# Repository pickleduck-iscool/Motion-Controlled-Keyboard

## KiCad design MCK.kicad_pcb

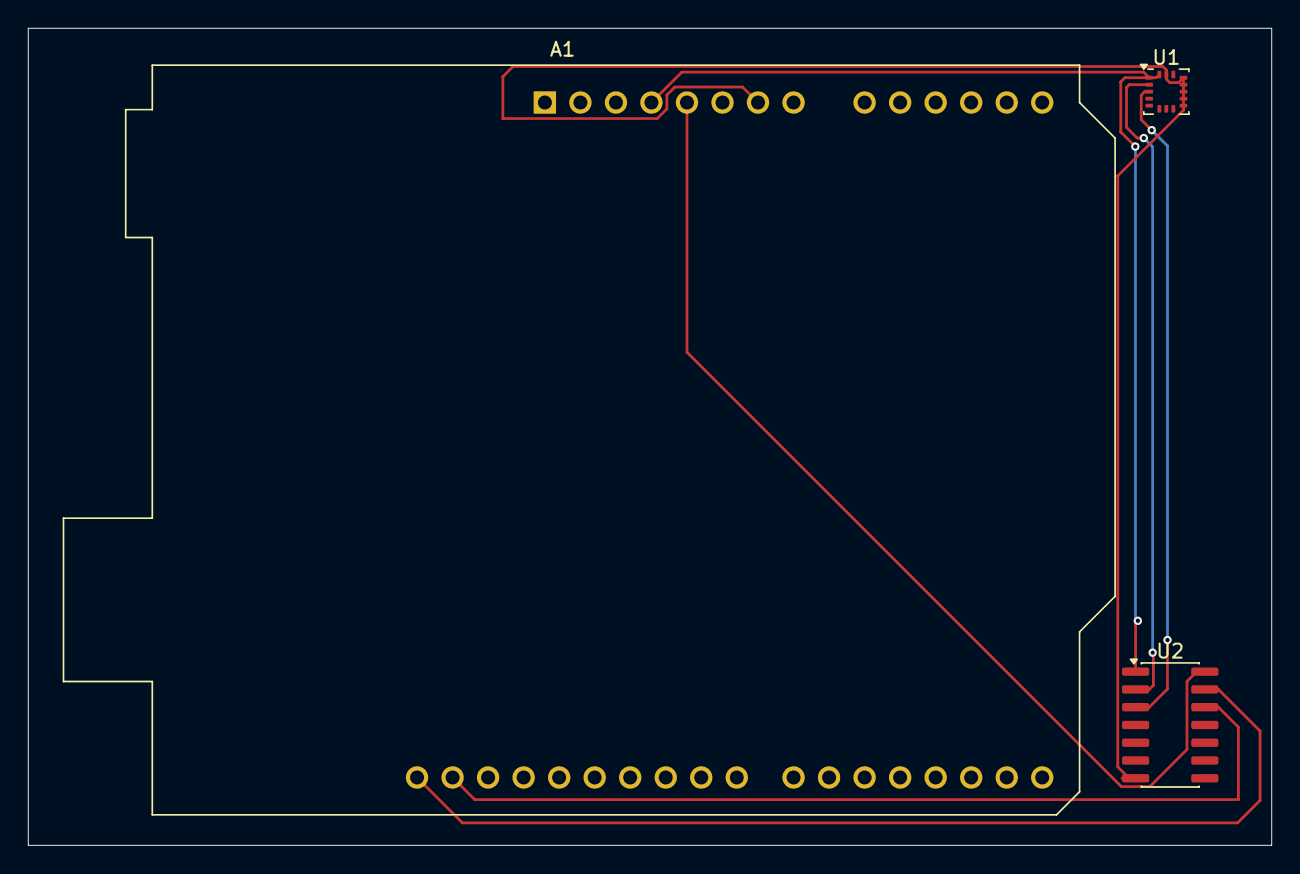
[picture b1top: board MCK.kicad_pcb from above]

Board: 2 copper layers, 88.9 x 58.4 mm, 3 parts (0 on the bottom side), 7 nets.

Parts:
A1: Arduino_Leonardo; Arduino_UNO_R3
U1: ICM-20602; LGA-16_3x3mm_P0.5mm_LayoutBorder3x5y
U2: TXS0104ED; SOIC-14_3.9x8.7mm_P1.27mm

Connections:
unnamed: A1.4 (3V3), U1.1 (VDDIO), U1.16 (VDD), U2.1 (V_{CCA})
unnamed: A1.5 (+5V), U2.14 (V_{CCB})
unnamed: A1.32 (SCL/D3), U2.13 (B1)
unnamed: A1.31 (SDA/D2), U2.12 (B2)
unnamed: U1.2 (SCL/SPC), U2.2 (A1)
unnamed: U1.3 (SDA/SDI), U2.3 (A2)
unnamed: A1.7 (GND), U1.9 (GND), U1.10 (GND), U1.11 (GND), U1.12 (GND), U1.13 (GND), U1.15 (GND), U2.7 (GND)

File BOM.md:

# Hand Motion Keyboard – bill of materials

<!-- Generated by Half Life from project cmv2t30zv083401q3pdh1eyeq. Edits here are overwritten on the next sync. -->
<!-- Generated: 2026-10-12T02:02:27.321Z -->

> [!NOTE]
> This parts list is mirrored from [Half Life](https://halflife.hackclub.com). Editing it here will not change the platform's copy, and the next sync overwrites this file.

| Week | Tier | Parts funding |
| --- | --- | --- |
| Week 1 | Tier 1 | $30.00 |

| Part | What it's for | Qty | Unit | Total | Vendor |
| --- | --- | --- | --- | --- | --- |
| [Arduino Leonardo](https://store-usa.arduino.cc/products/arduino-leonardo-with-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 | Microcontroller | 1 | $23.80 | $23.80 | [Arduino](https://store-usa.arduino.cc/products/arduino-leonardo-with-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 |
| [TXS0104ED](https://www.ti.com/product/TXS0104E/part-details/TXS0104ED) | Logic Level Translation | 1 | $1.58 | $1.58 | [Texas Instruments](https://www.ti.com/product/TXS0104E/part-details/TXS0104ED) |
| [ICM-20602](https://www.amazon.com/MusRock-ICM-20602-Gyroscope-Accelerom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 | Accelerometer and Gyroscope | 1 | $12.99 | $12.99 | [Amazon](https://www.amazon.com/MusRock-ICM-20602-Gyroscope-Accelerom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 |
| **Parts subtotal** | — | — | — | **$38.37** | — |
| **Tax & shipping** | — | — | — | **$0.00** | — |
| **Total** | — | — | — | **$38.37** | — |

**$8.37 over the tier's funding.** Every tier gives a fixed amount for parts, so this needs cutting back or a higher tier.
